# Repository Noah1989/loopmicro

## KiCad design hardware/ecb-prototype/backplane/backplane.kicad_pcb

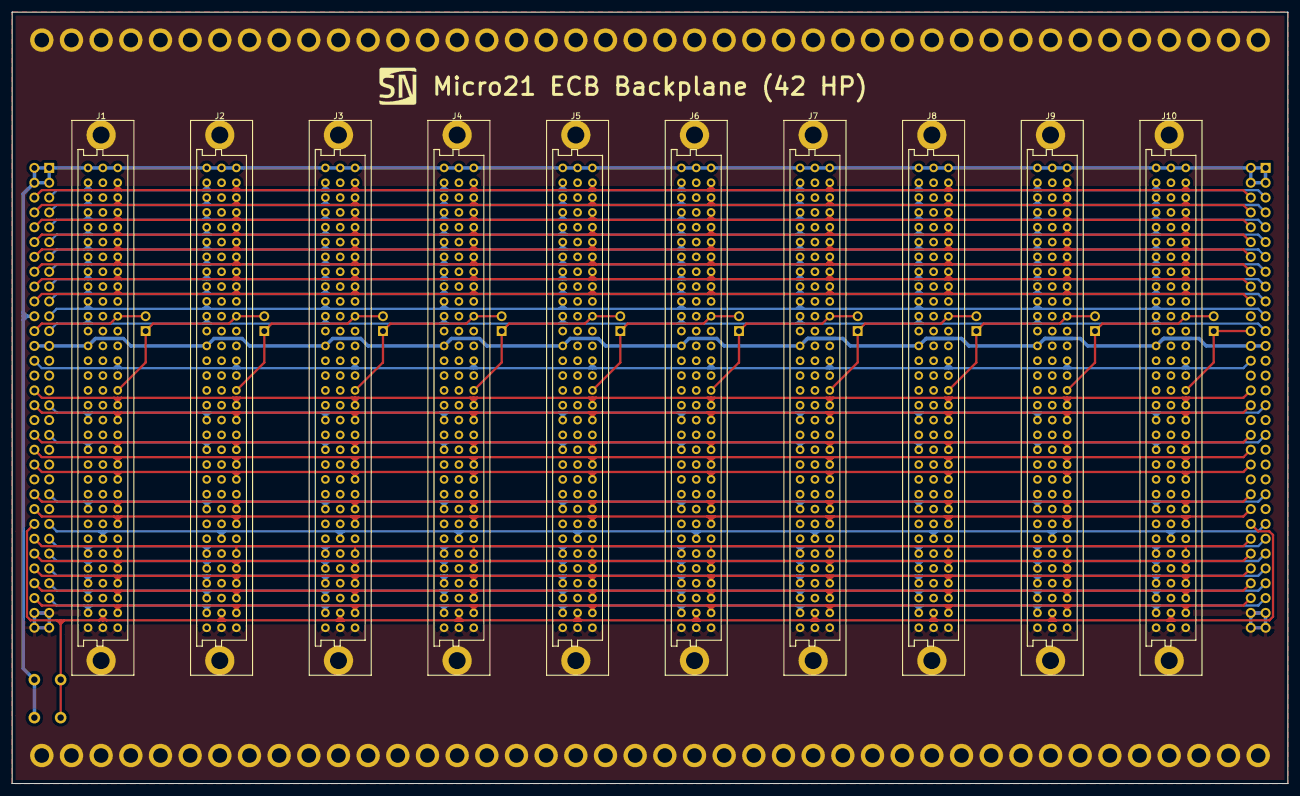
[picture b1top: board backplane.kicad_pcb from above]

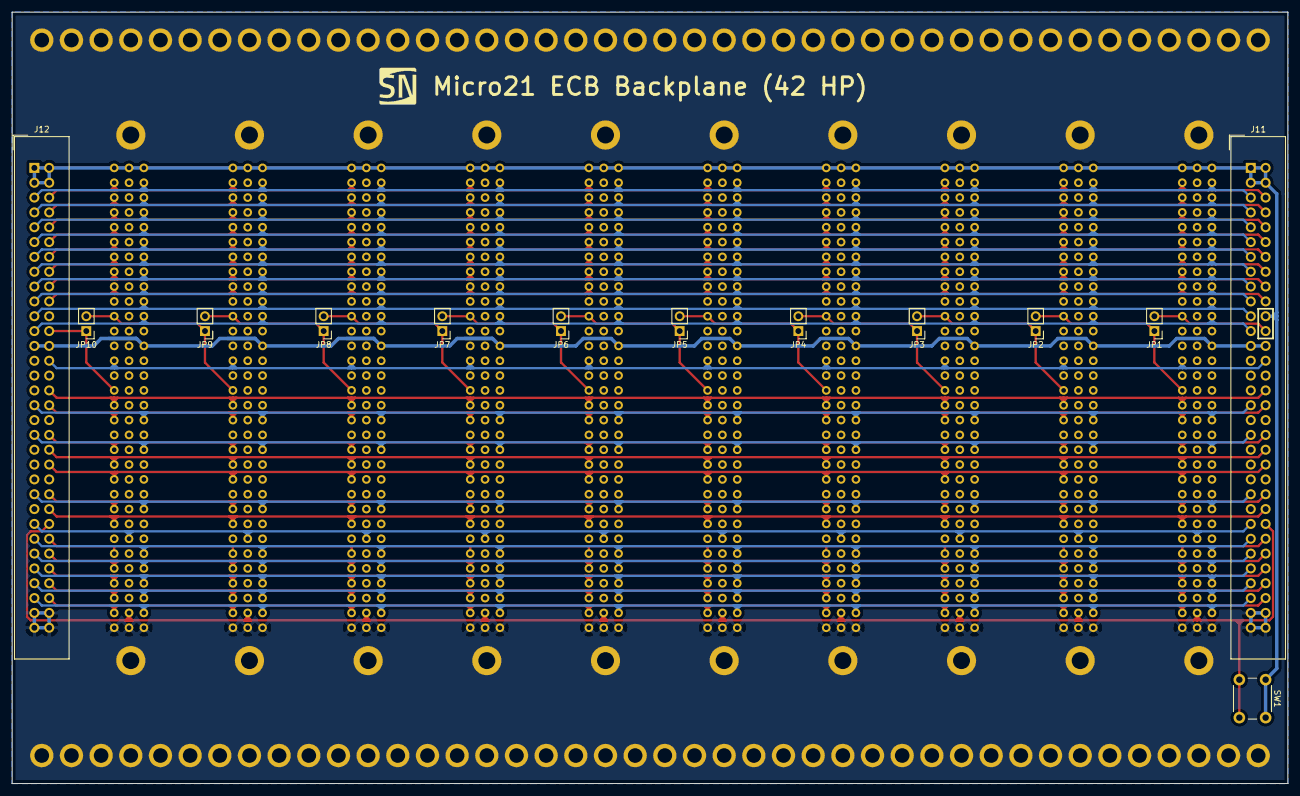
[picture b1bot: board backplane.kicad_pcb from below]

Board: 2 copper layers, 218.4 x 132.1 mm, 23 parts (13 on the bottom side), 55 nets.

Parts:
J1, J2, J3, J4, J5, J6, J7, J8, J9, J10: C96ABC; Socket_DIN41612-CaseC1-full-Female-96Pin-3rows
J11, J12: Conn_02x32_Odd_Even; IDC-Header_2x32_P2.54mm_Vertical
JP1, JP2, JP3, JP4, JP5, JP6, JP7, JP8, JP9, JP10: Jumper; PinHeader_1x02_P2.54mm_Vertical
SW1: SW_Push; SW_PUSH_6mm_H7.3mm

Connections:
+12V: J1.A13, J2.A13, J3.A13, J4.A13, J5.A13, J6.A13, J7.A13, J8.A13, J9.A13, J10.A13, J11.25, J11.26, J12.25, J12.26
+BATT: J1.A24, J2.A24, J3.A24, J4.A24, J5.A24, J6.A24, J7.A24, J8.A24, J9.A24, J10.A24, J11.45, J12.45
A0: J1.C5, J2.C5, J3.C5, J4.C5, J5.C5, J6.C5, J7.C5, J8.C5, J9.C5, J10.C5, J11.12, J12.12
A1: J1.C7, J2.C7, J3.C7, J4.C7, J5.C7, J6.C7, J7.C7, J8.C7, J9.C7, J10.C7, J11.16, J12.16
A2: J1.A6, J2.A6, J3.A6, J4.A6, J5.A6, J6.A6, J7.A6, J8.A6, J9.A6, J10.A6, J11.13, J12.13
A3: J1.C6, J2.C6, J3.C6, J4.C6, J5.C6, J6.C6, J7.C6, J8.C6, J9.C6, J10.C6, J11.14, J12.14
A4: J1.A7, J2.A7, J3.A7, J4.A7, J5.A7, J6.A7, J7.A7, J8.A7, J9.A7, J10.A7, J11.15, J12.15
A5: J1.A8, J2.A8, J3.A8, J4.A8, J5.A8, J6.A8, J7.A8, J8.A8, J9.A8, J10.A8, J11.17, J12.17
A6: J1.A9, J2.A9, J3.A9, J4.A9, J5.A9, J6.A9, J7.A9, J8.A9, J9.A9, J10.A9, J11.19, J12.19
A7: J1.C9, J2.C9, J3.C9, J4.C9, J5.C9, J6.C9, J7.C9, J8.C9, J9.C9, J10.C9, J11.20, J12.20
A8: J1.C8, J2.C8, J3.C8, J4.C8, J5.C8, J6.C8, J7.C8, J8.C8, J9.C8, J10.C8, J11.18, J12.18
A9: J1.A30, J2.A30, J3.A30, J4.A30, J5.A30, J6.A30, J7.A30, J8.A30, J9.A30, J10.A30, J11.57, J12.57
A10: J1.C18, J2.C18, J3.C18, J4.C18, J5.C18, J6.C18, J7.C18, J8.C18, J9.C18, J10.C18, J11.34, J12.34
A11: J1.C17, J2.C17, J3.C17, J4.C17, J5.C17, J6.C17, J7.C17, J8.C17, J9.C17, J10.C17, J11.32, J12.32
A12: J1.C27, J2.C27, J3.C27, J4.C27, J5.C27, J6.C27, J7.C27, J8.C27, J9.C27, J10.C27, J11.52, J12.52
A13: J1.A29, J2.A29, J3.A29, J4.A29, J5.A29, J6.A29, J7.A29, J8.A29, J9.A29, J10.A29, J11.55, J12.55
A14: J1.A18, J2.A18, J3.A18, J4.A18, J5.A18, J6.A18, J7.A18, J8.A18, J9.A18, J10.A18, J11.33, J12.33
A15: J1.C28, J2.C28, J3.C28, J4.C28, J5.C28, J6.C28, J7.C28, J8.C28, J9.C28, J10.C28, J11.54, J12.54
CLK: J1.C29, J2.C29, J3.C29, J4.C29, J5.C29, J6.C29, J7.C29, J8.C29, J9.C29, J10.C29, J11.56, J12.56
D0: J1.C2, J2.C2, J3.C2, J4.C2, J5.C2, J6.C2, J7.C2, J8.C2, J9.C2, J10.C2, J11.6, J12.6
D1: J1.C14, J2.C14, J3.C14, J4.C14, J5.C14, J6.C14, J7.C14, J8.C14, J9.C14, J10.C14, J11.28, J12.28
D2: J1.C4, J2.C4, J3.C4, J4.C4, J5.C4, J6.C4, J7.C4, J8.C4, J9.C4, J10.C4, J11.10, J12.10
D3: J1.A4, J2.A4, J3.A4, J4.A4, J5.A4, J6.A4, J7.A4, J8.A4, J9.A4, J10.A4, J11.9, J12.9
D4: J1.A5, J2.A5, J3.A5, J4.A5, J5.A5, J6.A5, J7.A5, J8.A5, J9.A5, J10.A5, J11.11, J12.11
D5: J1.A2, J2.A2, J3.A2, J4.A2, J5.A2, J6.A2, J7.A2, J8.A2, J9.A2, J10.A2, J11.5, J12.5
D6: J1.A3, J2.A3, J3.A3, J4.A3, J5.A3, J6.A3, J7.A3, J8.A3, J9.A3, J10.A3, J11.7, J12.7
D7: J1.C3, J2.C3, J3.C3, J4.C3, J5.C3, J6.C3, J7.C3, J8.C3, J9.C3, J10.C3, J11.8, J12.8
GND: J1.A32, J1.B32, J1.C32, J2.A32, J2.B32, J2.C32, J3.A32, J3.B32, J3.C32, J4.A32, J4.B32, J4.C32, J5.A32, J5.B32, J5.C32, J6.A32, J6.B32, J6.C32, J7.A32, J7.B32, J7.C32, J8.A32, J8.B32, J8.C32, J9.A32, J9.B32, J9.C32, J10.A32, J10.B32, J10.C32, J11.61, J11.62, J11.63, J11.64, J12.61, J12.62, J12.63, J12.64
unnamed: J1.C11, J11.24, JP1.2
unnamed: J1.C16, J2.C11, JP1.1, JP2.2
unnamed: J2.C16, J3.C11, JP2.1, JP3.2
unnamed: J3.C16, J4.C11, JP3.1, JP4.2
unnamed: J4.C16, J5.C11, JP4.1, JP5.2
unnamed: J5.C16, J6.C11, JP5.1, JP6.2
unnamed: J6.C16, J7.C11, JP6.1, JP7.2
unnamed: J7.C16, J8.C11, JP7.1, JP8.2
unnamed: J8.C16, J9.C11, JP8.1, JP9.2
unnamed: J9.C16, J10.C11, JP9.1, JP10.2
unnamed: J10.C16, J12.24, JP10.1
RESB: J1.B31, J2.B31, J3.B31, J4.B31, J5.B31, J6.B31, J7.B31, J8.B31, J9.B31, J10.B31, J11.50, J12.50, SW1.2
VCC: J1.A1, J1.B1, J1.C1, J2.A1, J2.B1, J2.C1, J3.A1, J3.B1, J3.C1, J4.A1, J4.B1, J4.C1, J5.A1, J5.B1, J5.C1, J6.A1, J6.B1, J6.C1, J7.A1, J7.B1, J7.C1, J8.A1, J8.B1, J8.C1, J9.A1, J9.B1, J9.C1, J10.A1, J10.B1, J10.C1, J11.1, J11.2, J11.3, J11.4, J11.22, J12.1, J12.2, J12.3, J12.4, SW1.1
~BUSAK: J1.A31, J2.A31, J3.A31, J4.A31, J5.A31, J6.A31, J7.A31, J8.A31, J9.A31, J10.A31, J11.59, J12.59
~BUSRQ: J1.A11, J2.A11, J3.A11, J4.A11, J5.A11, J6.A11, J7.A11, J8.A11, J9.A11, J10.A11, J11.23, J12.23
~HALT: J1.C25, J2.C25, J3.C25, J4.C25, J5.C25, J6.C25, J7.C25, J8.C25, J9.C25, J10.C25, J11.48, J12.48
~INT: J1.C21, J2.C21, J3.C21, J4.C21, J5.C21, J6.C21, J7.C21, J8.C21, J9.C21, J10.C21, J11.40, J12.40
~IORQ: J1.A27, J2.A27, J3.A27, J4.A27, J5.A27, J6.A27, J7.A27, J8.A27, J9.A27, J10.A27, J11.51, J12.51
~M1: J1.A20, J2.A20, J3.A20, J4.A20, J5.A20, J6.A20, J7.A20, J8.A20, J9.A20, J10.A20, J11.37, J12.37
~MREQ: J1.C30, J2.C30, J3.C30, J4.C30, J5.C30, J6.C30, J7.C30, J8.C30, J9.C30, J10.C30, J11.58, J12.58
~NMI: J1.C20, J2.C20, J3.C20, J4.C20, J5.C20, J6.C20, J7.C20, J8.C20, J9.C20, J10.C20, J11.38, J12.38
~RD: J1.C24, J2.C24, J3.C24, J4.C24, J5.C24, J6.C24, J7.C24, J8.C24, J9.C24, J10.C24, J11.46, J12.46
~RESET: J1.C31, J2.C31, J3.C31, J4.C31, J5.C31, J6.C31, J7.C31, J8.C31, J9.C31, J10.C31, J11.60, J12.60
~RFSH: J1.A28, J2.A28, J3.A28, J4.A28, J5.A28, J6.A28, J7.A28, J8.A28, J9.A28, J10.A28, J11.53, J12.53
~ROB: J1.B26, J2.B26, J3.B26, J4.B26, J5.B26, J6.B26, J7.B26, J8.B26, J9.B26, J10.B26, J11.49, J12.49
~WAIT: J1.A10, J2.A10, J3.A10, J4.A10, J5.A10, J6.A10, J7.A10, J8.A10, J9.A10, J10.A10, J11.21, J12.21
~WR: J1.C22, J2.C22, J3.C22, J4.C22, J5.C22, J6.C22, J7.C22, J8.C22, J9.C22, J10.C22, J11.42, J12.42

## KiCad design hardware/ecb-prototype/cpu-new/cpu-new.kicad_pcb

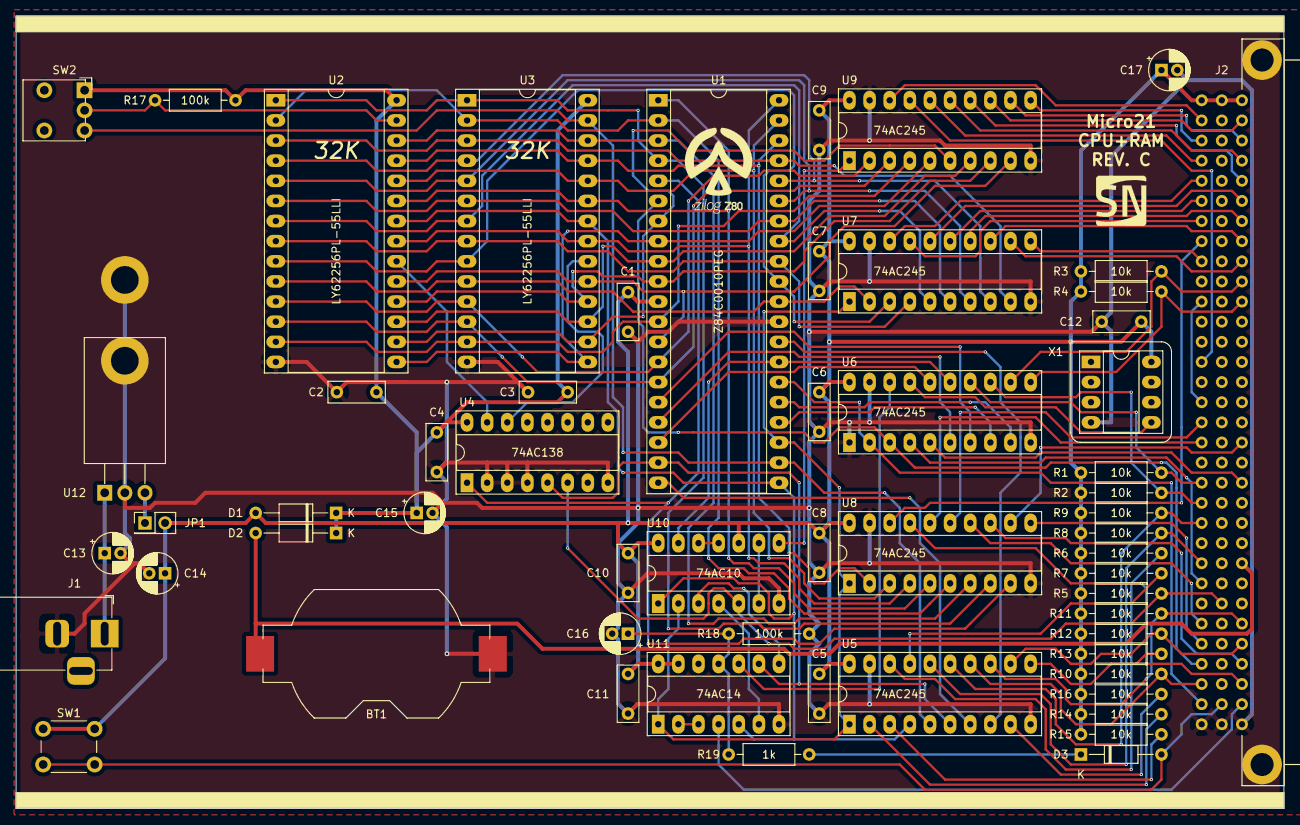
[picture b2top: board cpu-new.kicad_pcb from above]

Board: 2 copper layers, 160.0 x 100.0 mm, 58 parts (0 on the bottom side), 102 nets.

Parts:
BT1: CR2032; BatteryHolder_Keystone_1058_1x2032
C1, C2, C3, C4, C5, C6, C7, C8, C9, C10, C11, C12: 100nF; C_Rect_L7.0mm_W2.5mm_P5.00mm
C13, C14: 10µF; CP_Radial_D5.0mm_P2.00mm
C15, C16, C17: 1µF; CP_Radial_D5.0mm_P2.00mm
D1, D2, D3: BAT46; D_DO-35_SOD27_P10.16mm_Horizontal
J1: Barrel_Jack; BarrelJack_Horizontal
J2: C96ABC; Socket_DIN41612-CaseC1-full-Male-96Pin-3rows
JP1: Jumper; PinHeader_2x01_P2.54mm_Vertical
R1, R2, R3, R4, R5, R6, R7, R8, R9, R10, R11, R12, R13, R14, R15, R16: 10k; R_Axial_DIN0207_L6.3mm_D2.5mm_P10.16mm_Horizontal
R17, R18: 100k; R_Axial_DIN0207_L6.3mm_D2.5mm_P10.16mm_Horizontal
R19: 1k; R_Axial_DIN0207_L6.3mm_D2.5mm_P10.16mm_Horizontal
SW1: SW_Push; SW_PUSH_6mm_H5mm
SW2: SW_SPDT; SW_Lever_1P2T_NKK_GW12LxH
U1: Z84C0010PEG; DIP-40_W15.24mm_Socket_LongPads
U2, U3: LY62256PL-55LLI; DIP-28_W15.24mm_Socket_LongPads
U4: 74AC138; DIP-16_W7.62mm_Socket_LongPads
U5, U6, U7, U8, U9: 74AC245; DIP-20_W7.62mm_Socket_LongPads
U10: 74AC10; DIP-14_W7.62mm_Socket_LongPads
U11: 74AC14; DIP-14_W7.62mm_Socket_LongPads
U12: L7805; TO-220-3_Horizontal_TabDown
X1: 10MHz; DIP-8_W7.62mm_Socket_LongPads

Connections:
+BATT: BT1.1, D2.2, J2.A24
A0: J2.C5, U7.18
A1: J2.C7, U7.17
A2: J2.A6, U7.16
A3: J2.C6, U7.15
A4: J2.A7, U7.14
A5: J2.A8, U7.13
A6: J2.A9, U7.12
A7: J2.C9, U7.11
A8: J2.C8, U8.18
A9: J2.A30, U8.17
A10: J2.C18, U8.16
A11: J2.C17, U8.15
A12: J2.C27, U8.14
A13: J2.A29, U8.13
A14: J2.A18, U8.12
A15: J2.C28, U8.11
CLK: J2.C29, U1.6, U6.3
D0: J2.C2, U9.18
D1: J2.C14, U9.17
D2: J2.C4, U9.16
D3: J2.A4, U9.15
D4: J2.A5, U9.14
D5: J2.A2, U9.13
D6: J2.A3, U9.12
D7: J2.C3, U9.11
GND: BT1.2, C1.2, C2.2, C3.2, C4.2, C5.2, C6.2, C7.2, C8.2, C9.2, C10.2, C11.2, C12.1, C13.2, C14.2, C15.2, C16.2, C17.2, J1.2, J2.A32, J2.B32, J2.C32, R18.1, U1.29, U2.14, U3.14, U4.2, U4.3, U4.4, U4.8, U5.10, U5.19, U6.1, U6.10, U6.19, U7.10, U7.19, U8.10, U8.19, U9.10, U9.19, U10.7, U11.7, U12.2, X1.4
unnamed: C13.1, J1.1, U12.1
unnamed: C16.1, R18.2, R19.2, U11.11
unnamed: D3.1, R19.1
unnamed: J2.C11, J2.C16
unnamed: JP1.1, U12.3
unnamed: R6.1, U5.18
unnamed: R7.1, U5.17
unnamed: R13.1, U5.11
unnamed: R14.1, U5.2
unnamed: R15.1, U5.3
unnamed: R16.1, U5.9
unnamed: R17.2, SW2.2, U2.27
unnamed: SW2.3, U1.22, U3.27, U5.5
unnamed: U1.1, U2.23, U3.23, U8.5
unnamed: U1.2, U2.2, U3.2, U8.6
unnamed: U1.3, U2.26, U3.26, U8.7
unnamed: U1.4, U2.1, U3.1, U8.8
unnamed: U1.5, U4.1, U8.9
unnamed: U1.7, U2.16, U3.16, U9.6
unnamed: U1.8, U2.15, U3.15, U9.5
unnamed: U1.9, U2.17, U3.17, U9.7
unnamed: U1.10, U2.18, U3.18, U9.8
unnamed: U1.12, U2.13, U3.13, U9.4
unnamed: U1.13, U2.19, U3.19, U9.9
unnamed: U1.14, U2.11, U3.11, U9.2
unnamed: U1.15, U2.12, U3.12, U9.3
unnamed: U1.16, U6.7
unnamed: U1.17, U6.6
unnamed: U1.18, U6.16
unnamed: U1.19, U4.5, U5.6, U11.9
unnamed: U1.20, U5.7
unnamed: U1.21, U2.22, U3.22, U5.4, U10.1, U11.5
unnamed: U1.23, U5.1, U7.1, U8.1, U10.2, U11.1
unnamed: U1.24, U6.8
unnamed: U1.25, U6.9
unnamed: U1.27, U6.15, U10.13
unnamed: U1.28, U5.8
unnamed: U1.30, U2.10, U3.10, U7.2
unnamed: U1.31, U2.9, U3.9, U7.3
unnamed: U1.32, U2.8, U3.8, U7.4
unnamed: U1.33, U2.7, U3.7, U7.5
unnamed: U1.34, U2.6, U3.6, U7.6
unnamed: U1.35, U2.5, U3.5, U7.7
unnamed: U1.36, U2.4, U3.4, U7.8
unnamed: U1.37, U2.3, U3.3, U7.9
unnamed: U1.38, U2.25, U3.25, U8.2
unnamed: U1.39, U2.24, U3.24, U8.3
unnamed: U1.40, U2.21, U3.21, U8.4
unnamed: U2.20, U4.15
unnamed: U3.20, U4.14
unnamed: U6.17, X1.5
unnamed: U10.3, U11.8
unnamed: U10.4, U11.6
unnamed: U10.6, U10.9
unnamed: U9.1, U10.8
unnamed: U10.11, U10.12
unnamed: U11.2, U11.3
unnamed: U6.18, U11.10
RESB: D3.2, J2.B31, SW1.2
VCC: C1.1, C5.1, C6.1, C7.1, C8.1, C9.1, C10.1, C11.1, C12.2, C14.1, C17.1, D1.2, J2.A1, J2.B1, J2.C1, JP1.2, R1.2, R2.2, R3.2, R4.2, R5.2, R6.2, R7.2, R8.2, R9.2, R10.2, R11.2, R12.2, R13.2, R14.2, R15.2, R16.2, SW1.1, U1.11, U5.20, U6.20, U7.20, U8.20, U9.20, U10.10, U10.14, U11.13, U11.14, X1.8
VMEM: C2.1, C3.1, C4.1, C15.1, D1.1, D2.1, R17.1, SW2.1, U2.28, U3.28, U4.16
~BUSACK: J2.A31, U11.4
~BUSRQ: J2.A11, R4.1, U6.11
~EXM: J2.B26, R5.1, U4.6, U10.5
~HALT: J2.C25, U6.4
~INT: J2.C21, R2.1, U6.13
~IORQ: J2.A27, R11.1, U5.13
~M1: J2.A20, U6.5
~MREQ: J2.C30, R10.1, U5.14
~NMI: J2.C20, R1.1, U6.14
~RD: J2.C24, R8.1, U5.16
~RESET: J2.C31, U1.26, U6.2
~RFSH: J2.A28, R12.1, U5.12
~WAIT: J2.A10, R3.1, U6.12
~WR: J2.C22, R9.1, U5.15

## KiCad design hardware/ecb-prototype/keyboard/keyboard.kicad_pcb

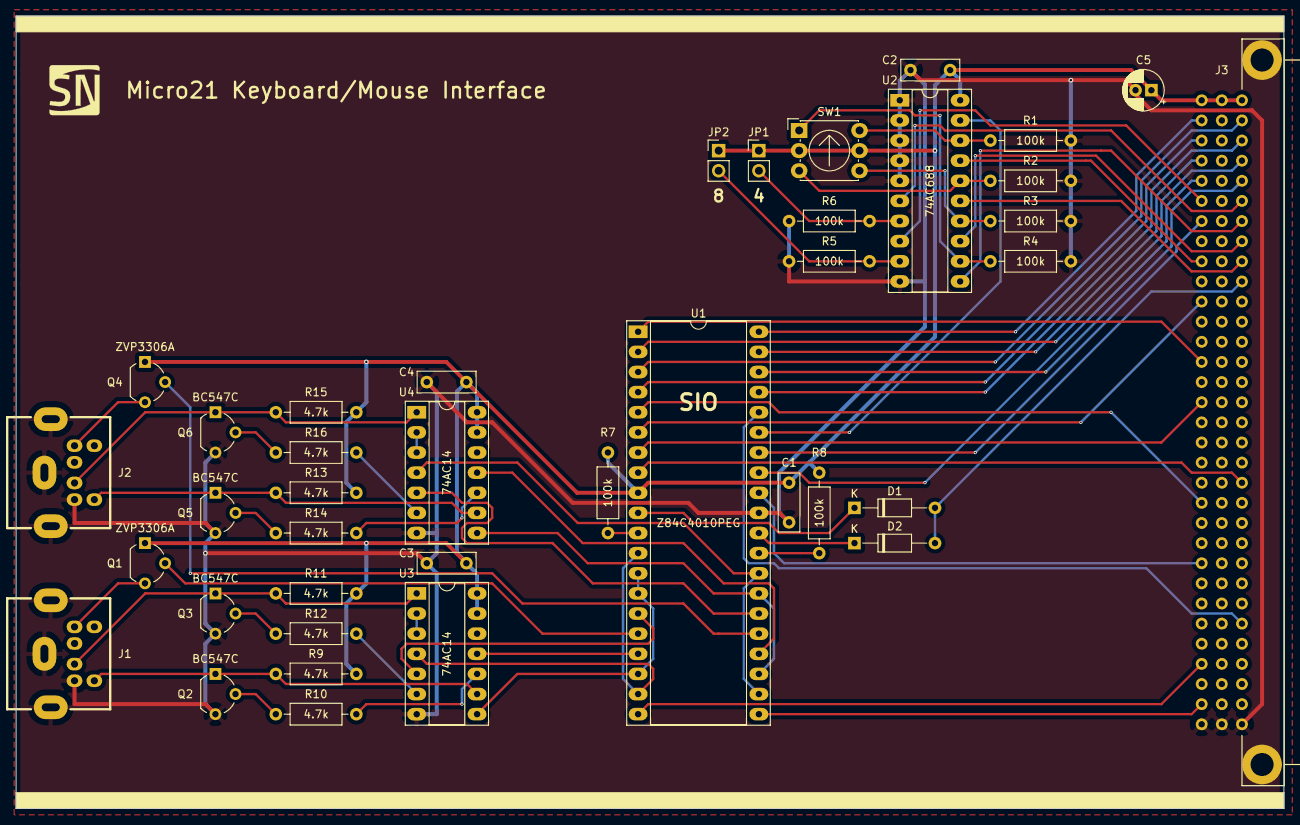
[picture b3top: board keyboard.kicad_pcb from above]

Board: 2 copper layers, 160.0 x 100.0 mm, 39 parts (0 on the bottom side), 64 nets.

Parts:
C1, C2, C3, C4: 100nF; C_Rect_L7.2mm_W2.5mm_P5.00mm_FKS2_FKP2_MKS2_MKP2
C5: CP; CP_Radial_D5.0mm_P2.00mm
D1, D2: BAT46; D_DO-35_SOD27_P10.16mm_Horizontal
J1, J2: Mini-DIN-6; Mini_DIN_6
J3: C96ABC; Socket_DIN41612-CaseC1-full-Male-96Pin-3rows
JP1, JP2: Jumper_NO_Small; PinHeader_1x02_P2.54mm_Vertical
Q1, Q4: ZVP3306A; TO-92_Wide
Q2, Q3, Q5, Q6: BC547C; TO-92_Wide
R1, R2, R3, R4, R5, R6, R7, R8: 100k; R_Axial_DIN0207_L6.3mm_D2.5mm_P10.16mm_Horizontal
R9, R10, R11, R12, R13, R14, R15, R16: 4.7k; R_Axial_DIN0207_L6.3mm_D2.5mm_P10.16mm_Horizontal
SW1: SW_Coded_SH-7050; Nidec_Copal_SH-7010C
U1: Z84C4010PEG; DIP-40_W15.24mm_Socket_LongPads
U2: 74AC688; DIP-20_W7.62mm_Socket_LongPads
U3, U4: 74AC14; DIP-14_W7.62mm_Socket_LongPads

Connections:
/ps2a/CLKOUT: U1.17, U3.11
/ps2a/DATAIN: U1.12, U1.19, U3.4
/ps2a/DATAOUT: U1.15, U3.5
/ps2a/~CLKIN: U1.13, U1.14, U1.18, U3.8
/ps2a/~PWRON: Q1.2, U1.16
/ps2b/CLKOUT: U1.24, U4.11
/ps2b/DATAIN: U1.22, U1.28, U4.4
/ps2b/DATAOUT: U1.26, U4.5
/ps2b/~CLKIN: U1.23, U1.27, U4.8
/ps2b/~PWRON: Q4.2, U1.25
A0: J3.C5, U1.33
A1: J3.C7, U1.34
A2: J3.A6, U2.6
A3: J3.C6, U2.8
A4: J3.A7, U2.11
A5: J3.A8, U2.13
A6: J3.A9, U2.15
A7: J3.C9, U2.17
CLK: J3.C29, U1.20
D0: J3.C2, U1.40
D1: J3.C14, U1.1
D2: J3.C4, U1.39
D3: J3.A4, U1.2
D4: J3.A5, U1.38
D5: J3.A2, U1.3
D6: J3.A3, U1.37
D7: J3.C3, U1.4
GND: C1.1, C2.2, C3.1, C4.1, C5.2, J1.3, J2.3, J3.A32, J3.B32, J3.C32, Q2.3, Q3.3, Q5.3, Q6.3, R1.2, R2.2, R3.2, R4.2, R5.2, R6.2, U1.31, U2.1, U2.2, U2.3, U2.4, U2.5, U2.10, U3.7, U4.7
IEI: J3.C11, U1.6
IEO: J3.C16, U1.7
unnamed: D1.1, U1.10
unnamed: D2.1, U1.30
unnamed: J1.1, Q3.1, R11.1, U3.1
unnamed: J1.4, Q1.3
unnamed: J1.5, Q2.1, R9.1, U3.9
unnamed: J2.1, Q6.1, R15.1, U4.1
unnamed: J2.4, Q4.3
unnamed: J2.5, Q5.1, R13.1, U4.9
unnamed: JP1.2, R6.1, U2.7
unnamed: JP2.2, R5.1, U2.9
unnamed: Q2.2, R10.1
unnamed: Q3.2, R12.1
unnamed: Q5.2, R14.1
unnamed: Q6.2, R16.1
unnamed: R1.1, SW1.8, U2.18
unnamed: R2.1, SW1.4, U2.16
unnamed: R3.1, SW1.2, U2.14
unnamed: R4.1, SW1.1, U2.12
unnamed: R7.2, U1.11
unnamed: R8.2, U1.29
unnamed: R10.2, U3.10
unnamed: R12.2, U3.6
unnamed: R14.2, U4.10
unnamed: R16.2, U4.6
unnamed: U1.35, U2.19
unnamed: U3.2, U3.3
unnamed: U4.2, U4.3
VCC: C1.2, C2.1, C3.2, C4.2, C5.1, J3.A1, J3.B1, J3.C1, JP1.1, JP2.1, Q1.1, Q4.1, R7.1, R8.1, R9.2, R11.2, R13.2, R15.2, SW1.C, U1.9, U2.20, U3.13, U3.14, U4.13, U4.14
~INT: J3.C21, U1.5
~IORQ: J3.A27, U1.36
~M1: J3.A20, U1.8
~RD: J3.C24, U1.32
~RESET: J3.C31, U1.21
~WAIT: D1.2, D2.2, J3.A10

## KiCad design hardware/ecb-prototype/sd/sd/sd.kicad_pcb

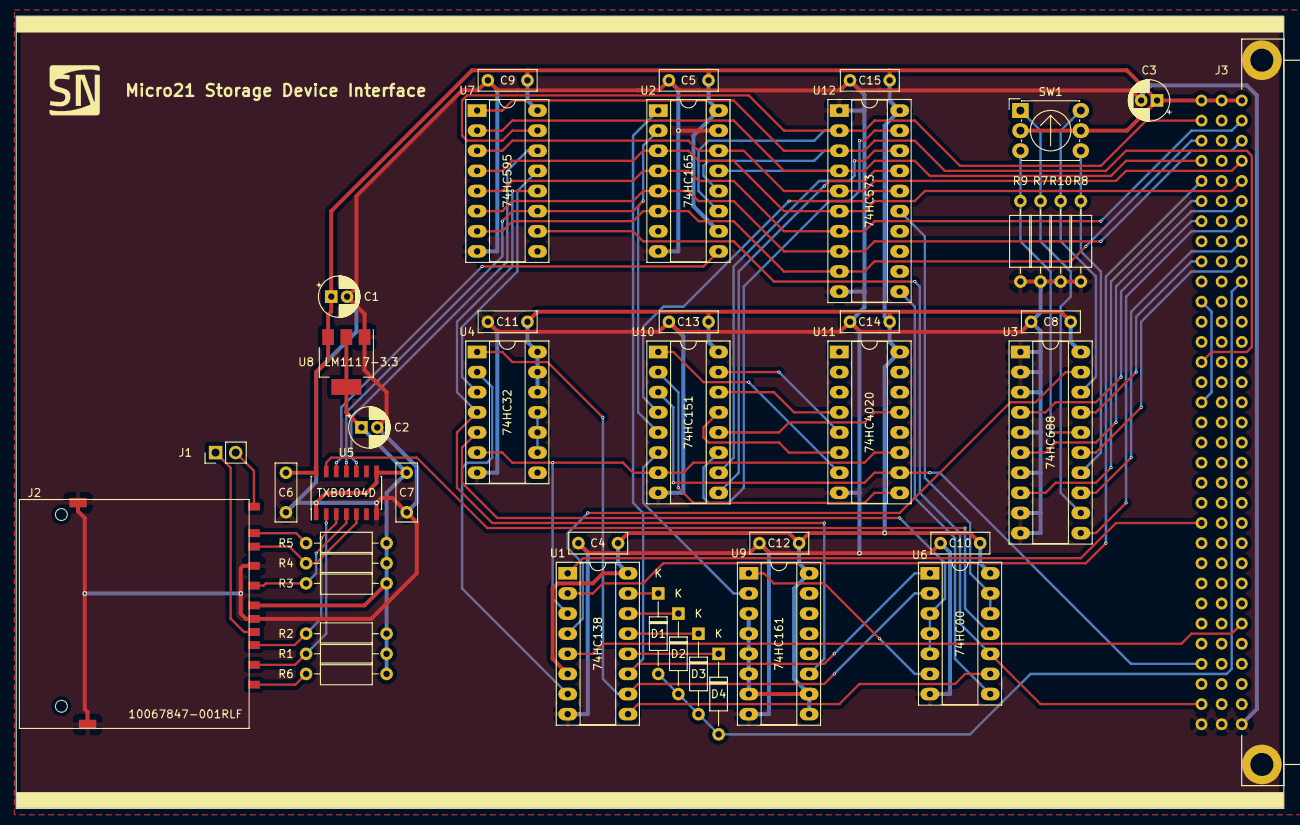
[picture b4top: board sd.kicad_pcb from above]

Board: 2 copper layers, 160.0 x 100.0 mm, 45 parts (0 on the bottom side), 69 nets.

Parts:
C1, C2, C3: CP_Small; CP_Radial_D5.0mm_P2.00mm
C4, C5, C6, C7, C8, C9, C10, C11, C12, C13, C14, C15: C; C_Rect_L7.2mm_W2.5mm_P5.00mm_FKS2_FKP2_MKS2_MKP2
D1, D2, D3, D4: BAT46; D_DO-35_SOD27_P10.16mm_Horizontal
J1: Conn_01x02_Male; PinHeader_1x02_P2.54mm_Vertical
J2: 10067847-001RLF; 10067847
J3: C96ABC; Socket_DIN41612-CaseC1-full-Male-96Pin-3rows
R1, R2, R3, R4, R5, R6, R7, R8, R9, R10: 100k; R_Axial_DIN0207_L6.3mm_D2.5mm_P10.16mm_Horizontal
SW1: SW_Coded_SH-7050; Nidec_Copal_SH-7010C
U1: 74HC138; DIP-16_W7.62mm_Socket_LongPads
U2: 74HC165; DIP-16_W7.62mm_Socket_LongPads
U3: 74HC688; DIP-20_W7.62mm_Socket_LongPads
U4: 74HC32; DIP-14_W7.62mm_Socket_LongPads
U5: TXB0104D; SOIC-14_3.9x8.7mm_P1.27mm
U6: 74HC00; DIP-14_W7.62mm_Socket_LongPads
U7: 74HC595; DIP-16_W7.62mm_Socket_LongPads
U8: LM1117-3.3; SOT-223-3_TabPin2
U9: 74HC161; DIP-16_W7.62mm_Socket_LongPads
U10: 74HC151; DIP-16_W7.62mm_Socket_LongPads
U11: 74HC4020; DIP-16_W7.62mm_Socket_LongPads
U12: 74HC573; DIP-20_W7.62mm_Socket_LongPads

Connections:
+3V3: C2.1, C7.1, J2.4, R1.1, R2.1, R3.1, R4.1, R5.1, R6.1, U5.1, U5.8, U8.2
+5V: C1.1, C3.1, C4.1, C5.1, C6.1, C8.1, C9.1, C10.1, C11.1, C12.1, C13.1, C14.1, C15.1, J3.A1, J3.B1, J3.C1, SW1.C, U1.6, U1.16, U2.10, U2.16, U3.20, U4.12, U4.13, U4.14, U5.14, U6.14, U7.16, U8.3, U9.3, U9.4, U9.5, U9.6, U9.7, U9.9, U9.10, U9.16, U10.16, U11.16, U12.20
/CS: J2.1, R1.2, U5.2
/DI: J2.2, R2.2, U5.3
/DO: J2.7, R4.2, U5.5
/SCLK: J2.5, R3.2, U5.4
A0: J3.C5, U1.2
A1: J3.C7, U3.4
A2: J3.A6, U3.6
A3: J3.C6, U3.8
A4: J3.A7, U3.11
A5: J3.A8, U3.13
A6: J3.A9, U3.15
A7: J3.C9, U3.17
CLK: J3.C29, U10.3, U11.10
D0: J3.C2, U2.11, U7.15, U12.2
D1: J3.C14, U2.12, U7.1, U12.3
D2: J3.C4, U2.13, U7.2, U12.4
D3: J3.A4, U2.14, U7.3, U12.5
D4: J3.A5, U2.3, U7.4, U12.6
D5: J3.A2, U2.4, U7.5, U12.7
D6: J3.A3, U2.5, U7.6, U12.8
D7: J3.C3, U2.6, U7.7, U12.9
GND: C1.2, C2.2, C3.2, C4.2, C5.2, C6.2, C7.2, C8.2, C9.2, C10.2, C11.2, C12.2, C13.2, C14.2, C15.2, J2.3, J2.6, J2.12, J2.13, J3.A32, J3.B32, J3.C32, R7.2, R8.2, R9.2, R10.2, U1.8, U2.8, U2.15, U3.1, U3.2, U3.3, U3.5, U3.7, U3.9, U3.10, U4.7, U5.7, U6.7, U7.8, U8.1, U9.8, U10.8, U11.8, U12.1, U12.10
unnamed: D1.1, U1.15
unnamed: D2.1, U1.14
unnamed: D3.1, U1.13
unnamed: D4.1, U1.12
unnamed: J1.1, J2.10
unnamed: J1.2, J2.11
unnamed: J2.8, R5.2
unnamed: J2.9, R6.2
unnamed: J3.C11, J3.C16
unnamed: R7.1, SW1.1, U3.12
unnamed: R8.1, SW1.2, U3.14
unnamed: R9.1, SW1.4, U3.16
unnamed: R10.1, SW1.8, U3.18
unnamed: U1.3, U4.6, U10.7, U11.11
unnamed: U1.4, U3.19
unnamed: U1.7, U4.2
unnamed: U1.9, U6.9
unnamed: U1.10, U4.1, U6.2
unnamed: U1.11, U2.1, U6.1
unnamed: U2.9, U5.12
unnamed: U4.3, U7.13
unnamed: U4.4, U7.12, U9.11
unnamed: U4.5, U6.3, U6.4, U6.5
unnamed: U4.9, U4.10, U4.11
unnamed: U5.10, U7.14
unnamed: U5.13, U6.11
unnamed: U6.6, U9.1
unnamed: U10.1, U11.7
unnamed: U10.2, U11.9
unnamed: U10.4, U12.16
unnamed: U2.2, U5.11, U7.11, U10.5
unnamed: U9.2, U10.6
unnamed: U10.9, U12.17
unnamed: U10.10, U12.18
unnamed: U10.11, U12.19
unnamed: U10.12, U11.13
unnamed: U10.13, U11.6
unnamed: U10.14, U11.4
unnamed: U10.15, U11.5
unnamed: U6.8, U12.11
unnamed: U6.12, U6.13, U12.15
~IORQ: J3.A27, U1.5
~RESET: J3.C31, U6.10, U7.10
~WAIT: D1.2, D2.2, D3.2, D4.2, J3.A10
~WR: J3.C22, U1.1

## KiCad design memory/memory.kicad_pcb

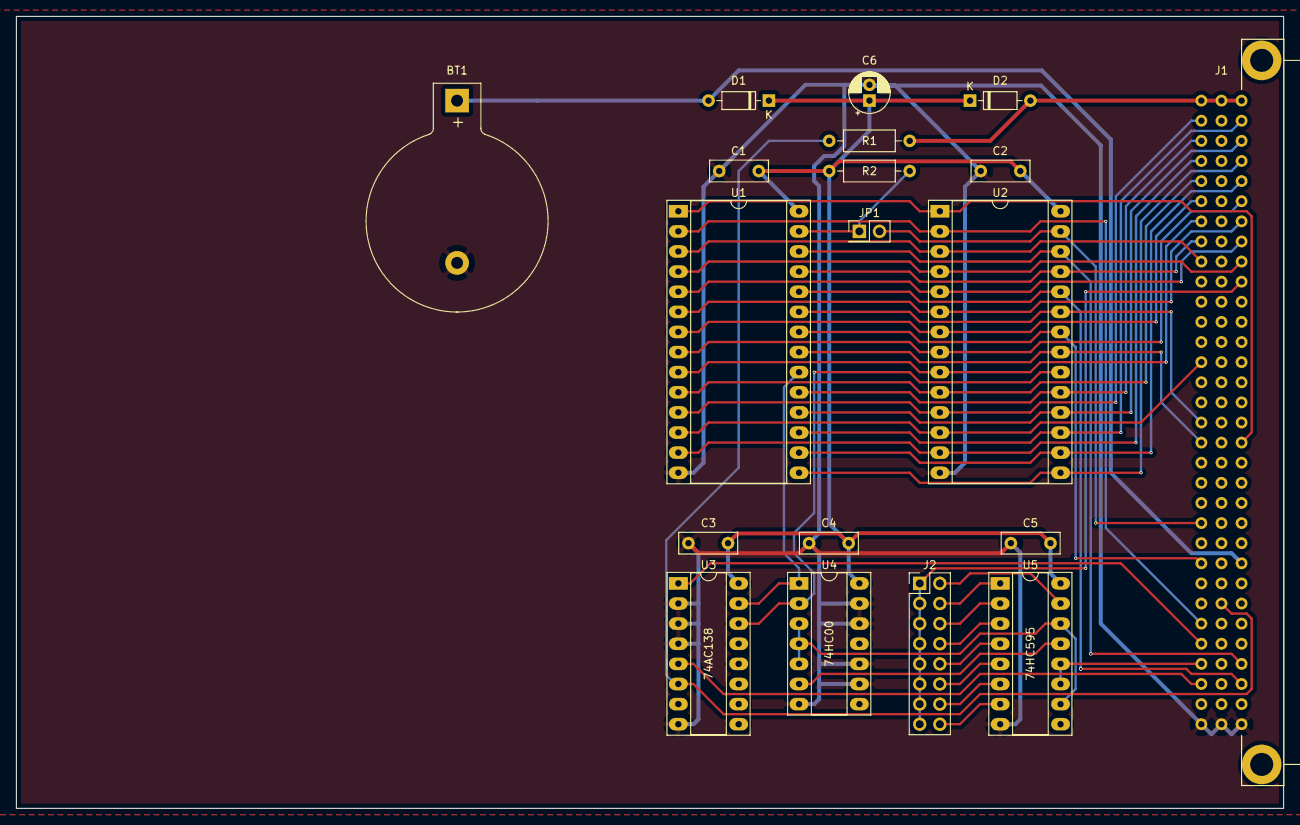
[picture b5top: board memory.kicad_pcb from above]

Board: 2 copper layers, 160.0 x 100.0 mm, 19 parts (0 on the bottom side), 47 nets.

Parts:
BT1: Battery_Cell; BatteryHolder_Keystone_103_1x20mm
C1, C2, C3, C4, C5: C_Small; C_Rect_L7.2mm_W2.5mm_P5.00mm_FKS2_FKP2_MKS2_MKP2
C6: CP1; CP_Radial_D5.0mm_P2.00mm
D1, D2: D_ALT; D_DO-35_SOD27_P7.62mm_Horizontal
J1: C96ABC; Socket_DIN41612-CaseC1-full-Male-96Pin-3rows
J2: Conn_02x08_Odd_Even; PinHeader_2x08_P2.54mm_Vertical
JP1: Jumper; PinHeader_2x01_P2.54mm_Vertical
R1, R2: R; R_Axial_DIN0207_L6.3mm_D2.5mm_P10.16mm_Horizontal
U1, U2: LY62256PL-55LLI; DIP-28_W15.24mm_Socket_LongPads
U3: 74AC138; DIP-16_W7.62mm_Socket_LongPads
U4: 74HC00; DIP-14_W7.62mm_Socket_LongPads
U5: 74HC595; DIP-16_W7.62mm_Socket_LongPads

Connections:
+BATT: BT1.1, D1.2, J1.A24
A0: J1.C5, U1.10, U2.10
A1: J1.C7, U1.9, U2.9
A2: J1.A6, U1.8, U2.8
A3: J1.C6, U1.7, U2.7
A4: J1.A7, U1.6, U2.6
A5: J1.A8, U1.5, U2.5
A6: J1.A9, U1.4, U2.4
A7: J1.C9, U1.3, U2.3
A8: J1.C8, U1.25, U2.25
A9: J1.A30, U1.24, U2.24
A10: J1.C18, U1.21, U2.21
A11: J1.C17, U1.23, U2.23
A12: J1.C27, U1.2, U2.2
A13: J1.A29, U1.26, U2.26
A14: J1.A18, U1.1, U2.1
A15: J1.C28, U3.1
CLK: J1.C29, U5.11, U5.12
D0: J1.C2, U1.11, U2.11
D1: J1.C14, U1.12, U2.12
D2: J1.C4, U1.13, U2.13
D3: J1.A4, U1.15, U2.15
D4: J1.A5, U1.16, U2.16
D5: J1.A2, U1.17, U2.17
D6: J1.A3, U1.18, U2.18
D7: J1.C3, U1.19, U2.19
GND: BT1.2, C1.2, C2.2, C3.2, C4.2, C5.2, C6.2, J1.A32, J1.B32, J1.C32, U1.14, U2.14, U3.2, U3.3, U3.4, U3.8, U4.7, U4.9, U4.10, U4.12, U4.13, U5.8
unnamed: J2.2, U5.15
unnamed: J2.4, U5.1
unnamed: J2.6, U5.2
unnamed: J2.8, U5.3
unnamed: J2.10, U5.4
unnamed: J2.12, U5.5
unnamed: J2.14, U5.6
unnamed: J2.16, U5.7
unnamed: JP1.1, R2.2, U1.27
unnamed: U1.20, U3.15, U4.1
unnamed: U2.20, U3.14, U4.2
unnamed: U4.3, U4.4, U4.5, U5.10, U5.14
unnamed: U4.6, U5.13
VCC: D2.2, J1.A1, J1.B1, J1.C1, R1.2
VMEM: C1.1, C2.1, C3.1, C4.1, C5.1, C6.1, D1.1, D2.1, R2.1, U1.28, U2.28, U3.16, U4.14, U5.16
~MREQ: J1.C30, U3.5
~RD: J1.C24, U1.22, U2.22
~ROB: J1.B26, R1.1, U3.6
~WAIT: J1.A10, J2.1, J2.3, J2.5, J2.7, J2.9, J2.11, J2.13, J2.15
~WR: J1.C22, JP1.2, U2.27
